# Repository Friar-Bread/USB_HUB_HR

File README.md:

# USB_HUB_HR
This project is for a compact USB hub. The hub uses a cable so that it is simpler and more versatile than the ordinary USB hub with a built in cable. The hub has both USB A and USB C ports for more options.
I made this project because I needed a USB hub to plub more peripherals into my PC. I also wanted to learn how USB and USB-C works. I learned a lot such as how to implement the resistors to make USB-C work. This was a farely simple project but I did lots of research on the parts. Additionally I learned about PCBA.
I followed this hackclub tutorial for some information on how to use the main IC. https://jams.hackclub.com/batch/usb-hub

CAD:

Onshape Link: https://cad.onshape.com/documents/d5f640465120f8047014c2e7/w/34da3dbbf4f363c2762e4589/e/4efec6a61c7e7d5025950684?renderMode=0&uiState=6938ea4b7058b2490eb946d4

Schematic:

PCB:

BOM:
| Item             | Description     | Quantity | Min Order #     | Price  |
| ---------------- | --------------- | -------- | --------------- | ------ |
| PCBA             | Manufacturing   | 1        | 5               | $31.61 |
| 3D Printed Shell | I'm printing it | 1        | 1               | $0     |
|                  |                 |          | Total with Tax: | $31.61 |

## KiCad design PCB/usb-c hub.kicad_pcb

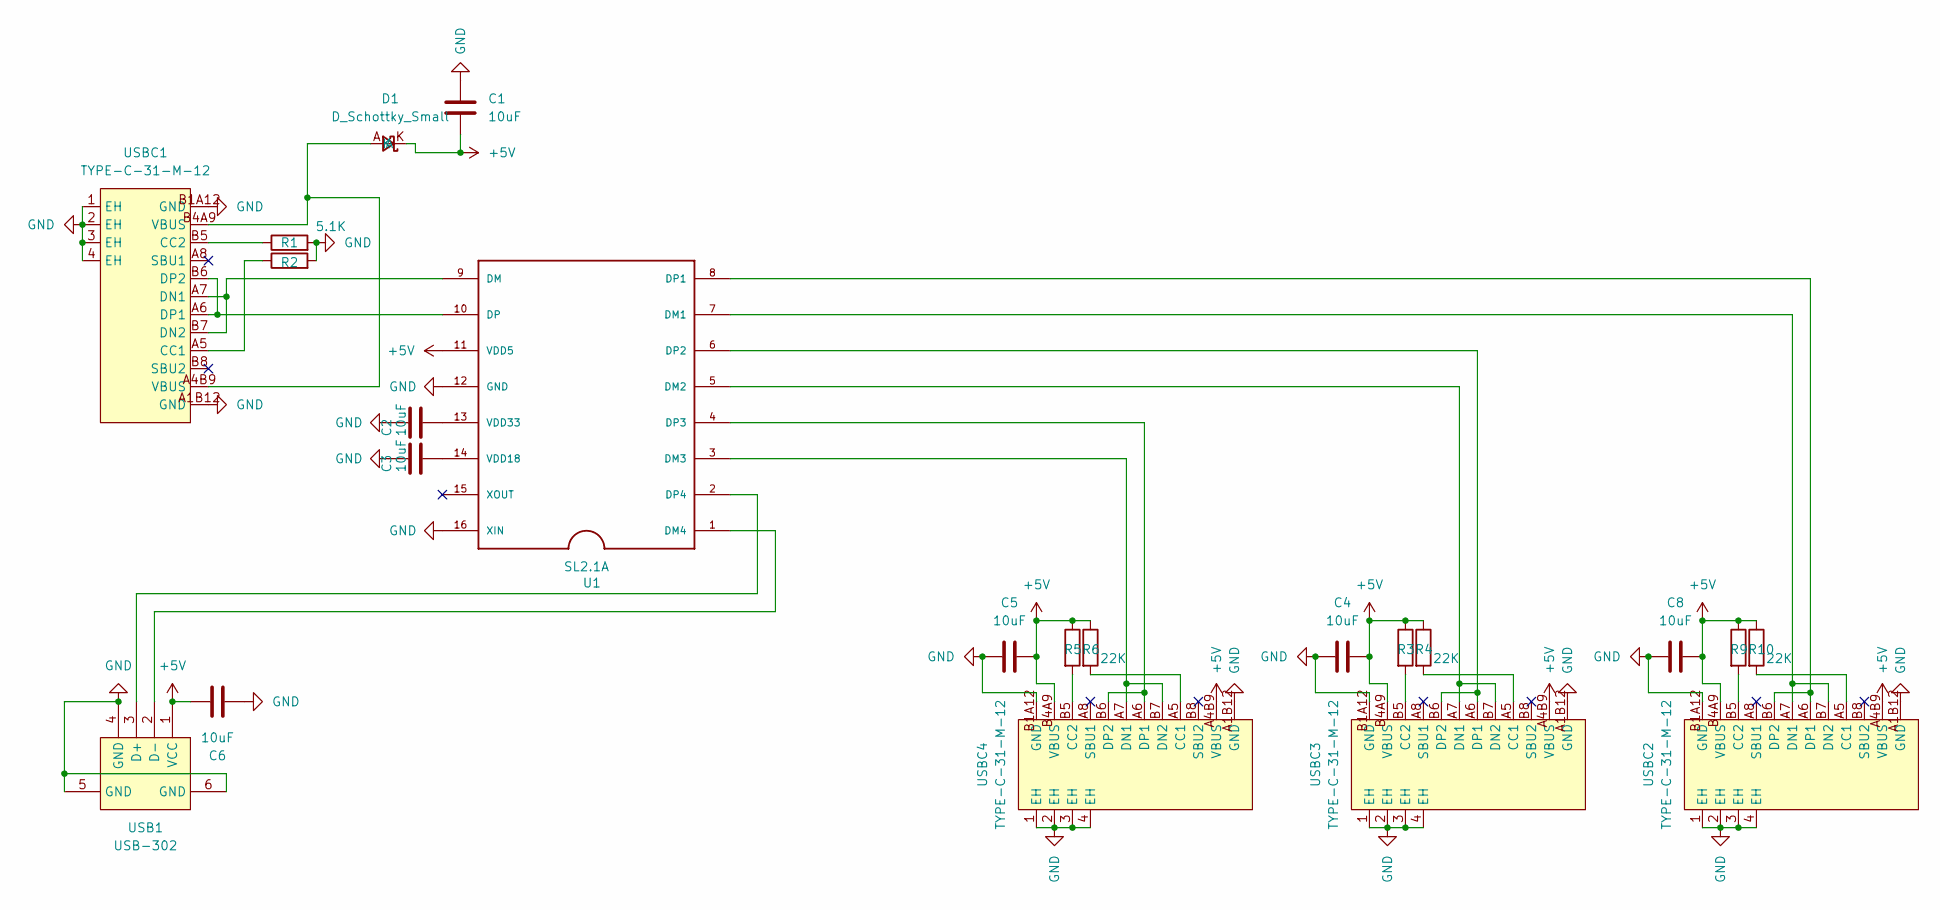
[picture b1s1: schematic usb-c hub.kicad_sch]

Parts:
C1, C2, C3, C4, C5, C6, C8: 10uF; CAPC1608X90N
D1: D_Schottky_Small; DIO_MM3Z3V0T1G
R1, R2: 5.1K; R0603
R3, R4, R5, R6, R9, R10: 22K; R0603
U1: SL2.1A; SO16
USB1: USB-302; USB-A-TH_USB-302-T; LCSC Part C112456
USBC1, USBC2, USBC3, USBC4: TYPE-C-31-M-12; USB-C_SMD-TYPE-C-31-M-12_1; LCSC Part C165948

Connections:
+5V: C1.2, C4.2, C5.2, C6.2, C8.2, D1.K, R3.1, R4.1, R5.1, R6.1, R9.1, R10.1, U1.11 (VDD5), USB1.1 (VCC), USBC2.A4B9 (VBUS), USBC2.B4A9 (VBUS), USBC3.A4B9 (VBUS), USBC3.B4A9 (VBUS), USBC4.A4B9 (VBUS), USBC4.B4A9 (VBUS)
GND: C1.1, C2.1, C3.1, C4.1, C5.1, C6.1, C8.1, R1.2, R2.2, U1.12 (GND), U1.16 (XIN), USB1.4 (GND), USB1.5 (GND), USB1.6 (GND), USBC1.1 (EH), USBC1.2 (EH), USBC1.3 (EH), USBC1.4 (EH), USBC1.A1B12 (GND), USBC1.B1A12 (GND), USBC2.1 (EH), USBC2.2 (EH), USBC2.3 (EH), USBC2.4 (EH), USBC2.A1B12 (GND), USBC2.B1A12 (GND), USBC3.1 (EH), USBC3.2 (EH), USBC3.3 (EH), USBC3.4 (EH), USBC3.A1B12 (GND), USBC3.B1A12 (GND), USBC4.1 (EH), USBC4.2 (EH), USBC4.3 (EH), USBC4.4 (EH), USBC4.A1B12 (GND), USBC4.B1A12 (GND)
unnamed: D1.A, USBC1.A4B9 (VBUS), USBC1.B4A9 (VBUS)
unnamed: U1.7 (DM1), USBC2.A7 (DN1), USBC2.B7 (DN2)
unnamed: U1.5 (DM2), USBC3.A7 (DN1), USBC3.B7 (DN2)
unnamed: U1.3 (DM3), USBC4.A7 (DN1), USBC4.B7 (DN2)
unnamed: U1.1 (DM4), USB1.2 (D-)
unnamed: U1.9 (DM), USBC1.A7 (DN1), USBC1.B7 (DN2)
unnamed: U1.8 (DP1), USBC2.A6 (DP1), USBC2.B6 (DP2)
unnamed: U1.6 (DP2), USBC3.A6 (DP1), USBC3.B6 (DP2)
unnamed: U1.4 (DP3), USBC4.A6 (DP1), USBC4.B6 (DP2)
unnamed: U1.2 (DP4), USB1.3 (D+)
unnamed: U1.10 (DP), USBC1.A6 (DP1), USBC1.B6 (DP2)
unnamed: C3.2, U1.14 (VDD18)
unnamed: C2.2, U1.13 (VDD33)
unnamed: R2.1, USBC1.A5 (CC1)
unnamed: R1.1, USBC1.B5 (CC2)
unnamed: R10.2, USBC2.A5 (CC1)
unnamed: R9.2, USBC2.B5 (CC2)
unnamed: R4.2, USBC3.A5 (CC1)
unnamed: R3.2, USBC3.B5 (CC2)
unnamed: R6.2, USBC4.A5 (CC1)
unnamed: R5.2, USBC4.B5 (CC2)

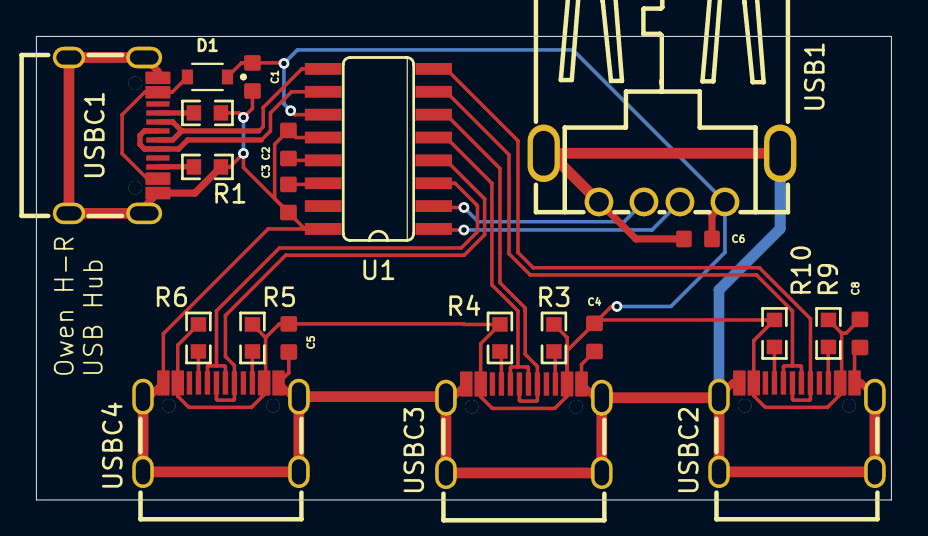
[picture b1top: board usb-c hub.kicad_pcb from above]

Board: 2 copper layers, 47.5 x 25.8 mm, 22 parts (0 on the bottom side), 23 nets.

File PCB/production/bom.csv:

Designator,Footprint,Quantity,Value,LCSC Part #
"C1, C2, C3, C4, C5, C6, C8",CAPC1608X90N,7,10uF,
D1,DIO_MM3Z3V0T1G,1,D_Schottky_Small,
"R1, R2",R0603,2,5.1K,
"R10, R3, R4, R5, R6, R9",R0603,6,22K,
U1,SO16,1,SL2.1A,
USB1,USB-A-TH_USB-302-T,1,USB-302,C112456
"USBC1, USBC2, USBC3, USBC4",USB-C_SMD-TYPE-C-31-M-12_1,4,TYPE-C-31-M-12,C165948

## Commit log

2025-12-10 Added PCB
2025-12-10 Added Images
2025-12-10 Changed a few files
2025-12-10 Added CAD Step file
2025-12-10 Updating production files
2025-12-10 Updating BOM
